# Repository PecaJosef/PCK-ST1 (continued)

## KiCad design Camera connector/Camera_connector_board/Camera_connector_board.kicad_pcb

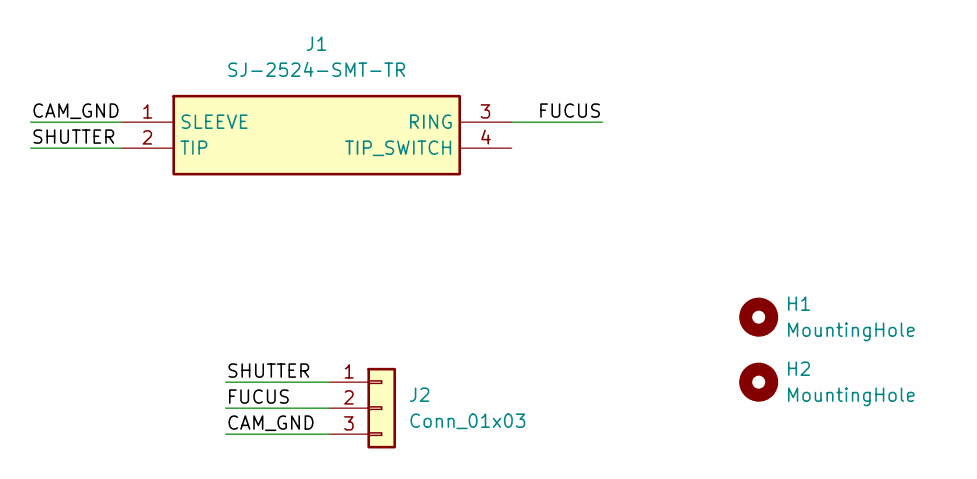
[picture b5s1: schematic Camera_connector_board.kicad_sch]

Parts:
H1, H2: MountingHole; MountingHole_3mm
J1: SJ-2524-SMT-TR; SJ2524SMTTR; Mouser Part Number 490-SJ-2524-SMT-TR
J2: Conn_01x03; JST_PH_B3B-PH-SM4-TB_1x03-1MP_P2.00mm_Vertical

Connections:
/CAM_GND: J1.1 (SLEEVE), J2.3
/FUCUS: J1.3 (RING), J2.2
/SHUTTER: J1.2 (TIP), J2.1

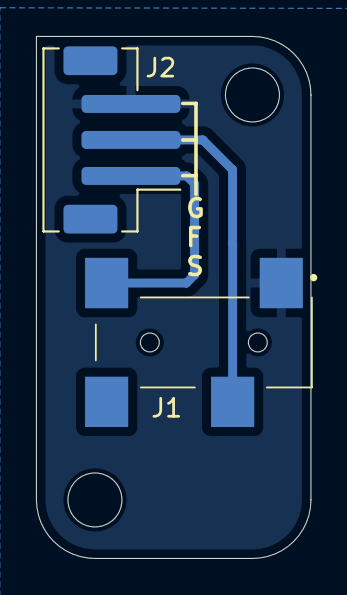
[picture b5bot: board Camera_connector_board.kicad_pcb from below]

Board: 2 copper layers, 15.2 x 29.0 mm, 4 parts (2 on the bottom side), 3 nets.

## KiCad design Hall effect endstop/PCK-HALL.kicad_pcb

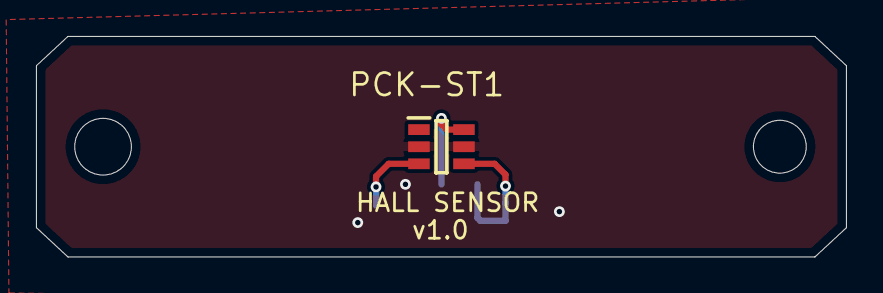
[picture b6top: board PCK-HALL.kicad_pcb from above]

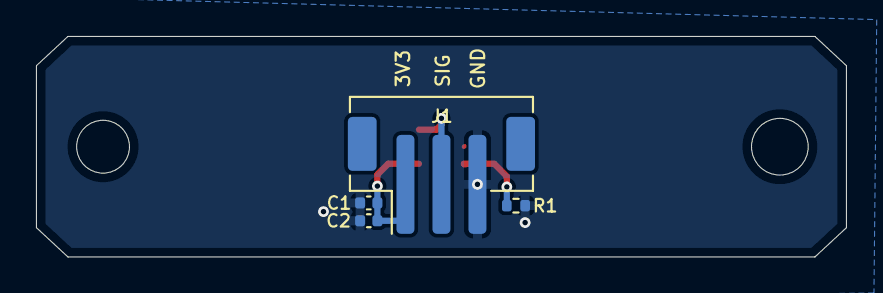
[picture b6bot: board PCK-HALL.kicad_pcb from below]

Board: 2 copper layers, 45.0 x 12.2 mm, 5 parts (4 on the bottom side), 4 nets.

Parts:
C1: 1uF; C_0402_1005Metric
C2: 100nF; C_0402_1005Metric
IC1: TMAG5328A1ZQDBVR; SOT95P280X145-6N
J1: Conn_01x03; JST_PH_B3B-PH-SM4-TB_1x03-1MP_P2.00mm_Vertical
R1: TBD; R_0402_1005Metric

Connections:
+3V3: C1.1, C2.1, IC1.4 (VCC), J1.1
GND: C1.2, C2.2, IC1.2 (GND), IC1.5 (TEST2), J1.3, R1.2
unnamed: IC1.3 (ADJ), R1.1
unnamed: IC1.6 (OUT), J1.2

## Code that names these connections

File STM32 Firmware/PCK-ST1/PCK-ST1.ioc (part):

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Mcu.Name=STM32L476R(C-E-G)Tx
Mcu.Package=LQFP64
Mcu.UserName=STM32L476RGTx
PA0.Mode=Asynchronous
PA0.Signal=UART4_TX
PA1.Mode=Asynchronous
PA1.Signal=UART4_RX
PA10.Mode=Asynchronous
PA10.Signal=USART1_RX
PA11.Mode=Device_Only
PA11.Signal=USB_OTG_FS_DM
PA12.Mode=Device_Only
PA12.Signal=USB_OTG_FS_DP
PA14\ (JTCK-SWCLK).GPIOParameters=GPIO_Label
PA14\ (JTCK-SWCLK).GPIO_Label=LED4
PA14\ (JTCK-SWCLK).Signal=GPIO_Output
PA15\ (JTDI).GPIOParameters=GPIO_Label
PA15\ (JTDI).GPIO_Label=LED3
PA15\ (JTDI).Signal=GPIO_Output
PA2.GPIOParameters=GPIO_PuPd,GPIO_Label,GPIO_ModeDefaultEXTI
PA2.GPIO_Label=ALT_LIM
PA2.GPIO_ModeDefaultEXTI=GPIO_MODE_IT_FALLING
PA2.GPIO_PuPd=GPIO_NOPULL
PA2.Signal=GPXTI2
PA3.GPIOParameters=GPIO_Label,GPIO_ModeDefaultEXTI
PA3.GPIO_Label=DEC_LIM
PA3.GPIO_ModeDefaultEXTI=GPIO_MODE_IT_FALLING
PA3.Signal=GPXTI3
PA4.GPIOParameters=GPIO_Label,GPIO_ModeDefaultEXTI
PA4.GPIO_Label=RA_LIM
PA4.GPIO_ModeDefaultEXTI=GPIO_MODE_IT_FALLING
PA4.Signal=GPXTI4
PA5.GPIOParameters=GPIO_Label
PA5.GPIO_Label=AZ_EN
PA5.Signal=GPIO_Output
PA6.GPIOParameters=GPIO_Label
PA6.GPIO_Label=AZ_DIR
PA6.Signal=GPIO_Output
PA7.GPIOParameters=GPIO_Speed,GPIO_Label
PA7.GPIO_Label=AZ_STEP
PA7.GPIO_Speed=GPIO_SPEED_FREQ_LOW
PA7.Signal=GPIO_Output
PA9.Mode=Asynchronous
PA9.Signal=USART1_TX
PB0.GPIOParameters=GPIO_Label
PB0.GPIO_Label=STEP_SLEEP_n
PB0.Signal=GPIO_Output
PB1.GPIOParameters=GPIO_Label
PB1.GPIO_Label=ALT_EN
PB1.Signal=GPIO_Output
PB10.GPIOParameters=GPIO_Label
PB10.GPIO_Label=ALT_STEP
PB10.Signal=GPIO_Output
PB11.GPIOParameters=GPIO_Label
PB11.GPIO_Label=ALT_FAULT_n
PB11.Signal=GPIO_Input
PB12.GPIOParameters=GPIO_Label
PB12.GPIO_Label=RA_EN
PB12.Signal=GPIO_Output
PB13.GPIOParameters=GPIO_Label
PB13.GPIO_Label=RA_DIR
PB13.Signal=GPIO_Output
PB14.GPIOParameters=GPIO_Label
PB14.GPIO_Label=RA_STEP
PB14.Mode=PWM Generation2 CH2N
PB14.Signal=TIM1_CH2N
PB15.GPIOParameters=GPIO_Label
PB15.GPIO_Label=RA_FAULT_n
PB15.Signal=GPIO_Input
PB2.GPIOParameters=GPIO_Label
PB2.GPIO_Label=ALT_DIR
PB2.Signal=GPIO_Output
PB3\ (JTDO-TRACESWO).GPIOParameters=GPIO_PuPd,GPIO_Label
PB3\ (JTDO-TRACESWO).GPIO_Label=PWR_STATE
PB3\ (JTDO-TRACESWO).GPIO_PuPd=GPIO_PULLUP
PB3\ (JTDO-TRACESWO).Signal=GPIO_Input
PB4\ (NJTRST).GPIOParameters=GPIO_Label
PB4\ (NJTRST).GPIO_Label=LED_USB
PB4\ (NJTRST).Signal=GPIO_Output
PB5.GPIOParameters=GPIO_Label
PB5.GPIO_Label=LED_DC
PB5.Signal=GPIO_Output
PB6.GPIOParameters=GPIO_Label
PB6.GPIO_Label=CAM_FOCUS
PB6.Signal=GPIO_Output
PB7.GPIOParameters=GPIO_Label
PB7.GPIO_Label=CAM_SHUTTER
PB7.Signal=GPIO_Output
PB8.GPIOParameters=GPIO_Label
PB8.GPIO_Label=RPI_PWR_EN
PB8.Signal=GPIO_Output
PB9.Signal=S_TIM17_CH1
PC0.Mode=I2C
PC0.Signal=I2C3_SCL
PC1.Mode=I2C
PC1.Signal=I2C3_SDA
PC10.GPIOParameters=GPIO_Label
PC10.GPIO_Label=LED2
PC10.Signal=GPIO_Output
PC11.GPIOParameters=GPIO_Label
PC11.GPIO_Label=LED1
PC11.Signal=GPIO_Output
PC12.Mode=Asynchronous
PC12.Signal=UART5_TX
PC13.GPIOParameters=GPIO_Label
PC13.GPIO_Label=PWR_BTN_LED
PC13.Signal=GPIO_Output
PC14-OSC32_IN\ (PC14).GPIOParameters=GPIO_Label
PC14-OSC32_IN\ (PC14).GPIO_Label=PWR_BTN
PC14-OSC32_IN\ (PC14).Signal=GPIO_Input
PC15-OSC32_OUT\ (PC15).GPIOParameters=GPIO_Label,GPIO_ModeDefaultEXTI
PC15-OSC32_OUT\ (PC15).GPIO_Label=AZ_LIM
PC15-OSC32_OUT\ (PC15).GPIO_ModeDefaultEXTI=GPIO_MODE_IT_FALLING
PC15-OSC32_OUT\ (PC15).Signal=GPXTI15
PC3.Signal=ADCx_IN4
PC4.GPIOParameters=GPIO_Label
PC4.GPIO_Label=AZ_FAULT_n
PC4.Signal=GPIO_Input
PC6.GPIOParameters=GPIO_Label
PC6.GPIO_Label=DEC_EN
PC6.Signal=GPIO_Output
PC7.GPIOParameters=GPIO_Label
PC7.GPIO_Label=DEC_DIR
PC7.Signal=GPIO_Output
PC8.GPIOParameters=GPIO_Speed,GPIO_Label
PC8.GPIO_Label=DEC_STEP
PC8.GPIO_Speed=GPIO_SPEED_FREQ_HIGH
PC8.Signal=S_TIM8_CH3
PC9.GPIOParameters=GPIO_Label
PC9.GPIO_Label=DEC_FAULT_n
PC9.Signal=GPIO_Input
PD2.Mode=Asynchronous
PD2.Signal=UART5_RX
PH0-OSC_IN\ (PH0).Mode=HSE-External-Oscillator
PH0-OSC_IN\ (PH0).Signal=RCC_OSC_IN
PH1-OSC_OUT\ (PH1).Mode=HSE-External-Oscillator
PH1-OSC_OUT\ (PH1).Signal=RCC_OSC_OUT
RCC.HSE_VALUE=16000000
RCC.SYSCLKFreq_VALUE=64000000
RCC.SYSCLKSource=RCC_SYSCLKSOURCE_PLLCLK
board=custom

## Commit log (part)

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2025-07-26 Added FW
2025-07-28 updt
2025-08-05 Added stepper control
2025-08-15 Updated resistor values
2025-08-15 Added gps.c and gps.h
2025-08-16 Updated endstops routing
2025-08-16 Added GPS and started homing functions
2025-08-16 Updated GPS - tested outside
2025-08-28 Power up idle, warm up state almost done
2025-09-10 Updated homing cycle
2025-09-13 Updated layout v0.2
2025-10-04 As built update
2025-10-04 As built updated
2025-10-10 UART commands
2025-10-15 Added Command list
2025-11-02 Added $MOVE command parsing
2025-11-04 updated AXIS_MOVING
2025-12-23 Added STEP file
2025-12-23 Main board updated to v0.3
2025-12-24 Added design change notes
2025-12-26 pd s nma update
2026-01-03 schema updated
2026-01-14 Added JST PH connector 3D model to the design
2026-01-14 Added Camera remote shutter breakout board
2026-01-17 Added pckdev from RPi
2026-01-18 Main board v0.3 to be manufactured
2026-01-18 V1.0 - manufacturing
2026-01-24 sw update
2026-01-28 Added $ALIGN and $SHUTDOWN command - to be tested
2026-01-28 Updated file names
2026-01-30 Added $PA command parsing
2026-02-03 Added part numbers for simpler ordering
2026-02-07 Rough alignment procedure prototype
2026-02-13 As built v0.3
2026-02-14 Fixed $PA:DEV response
2026-02-14 Fixed camera behavior
2026-02-14 Optimized find_polaris function
2026-02-14 Updated Main board to v1.0
2026-02-14 Updated control loop - alignment
2026-02-14 Creted new version of flex PCB for PA camera
2026-02-14 Created connector board for RPi connection and easier wiring
2026-02-15 Updated for testing v1
2026-02-15 Optimized star_processing
2026-02-15 fixed paths
2026-02-15 Optimized - coarse rotation + fine search
2026-02-15 Fixed long camera delay
2026-02-15 Fixed error with starless images
2026-02-17 Testing adjustment
2026-02-17 Updated image processing to reduce noise and overall brightness impact
2026-02-17 Update gain and exposure values - to be tested
2026-02-18 test
2026-03-07 Updated whole image processing/star processing
2026-03-07 Fixed errors in star_processing.py
2026-03-09 Updated star_processing.py, fixed some minor issues
2026-03-09 Enabled Debug mode
2026-03-12 Started working on telemetry Aligning seems to work after a few testings
2026-03-12 telemetry
2026-03-14 Updated GPS configuration
2026-03-14 Updated control loop behavior
2026-03-15 Updated telemetry
2026-03-15 Updated to v2.1
2026-03-15 Added R1 pull-up to RPI_PWR_EN
2026-03-15 Repo cleanup
2026-03-19 Updated V1.0 schematic values
2026-03-19 Updated to V0.2
2026-03-19 Added ALT, RA, DEC axis homing
2026-03-21 Added tracking functions
2026-04-03 Updated star processing and added CoR calculation
2026-04-03 deleted old file
2026-04-03 Updated CAPTURE command parsing
2026-04-03 capture updated
2026-04-03 Fixed CoR None issue
2026-04-03 Fixed command error
2026-04-04 Added CoR command handling, added HOMING, ALIGNING, TEST ALIGNING and ALIBRATING commands for switching states
2026-04-04 Added Python console
2026-04-07 Updated RA angle calculation
2026-04-13 Updated RA position
2026-04-13 Updated console
2026-04-13 Added astro coordinates tracking, goto fucntion and camera control Testing version
2026-04-16 Tracking logic updated
2026-04-16 Updated commands
2026-04-16 Idle command added
2026-04-16 Updated absolute paths
2026-04-16 Paths
2026-04-16 Updated power off commands
2026-04-16 Shutdown updated
2026-04-16 Updated for testing
2026-04-18 Renamed MCU sheet
2026-04-18 Updated RA coordinates updating after PA
2026-04-24 Added info messages
2026-04-24 Added CoR images writing to SD card for debug
2026-04-25 CoR updated
2026-04-25 Updated Polaris detection
2026-05-01 Updated goto updating wrongly
2026-05-01 sch update
2026-05-01 Added #COR info message
2026-05-01 Updated #COR info message
2026-05-03 Updated astro coordinates wrapping
2026-05-11 Removed old database files
2026-05-24 Code clean up
